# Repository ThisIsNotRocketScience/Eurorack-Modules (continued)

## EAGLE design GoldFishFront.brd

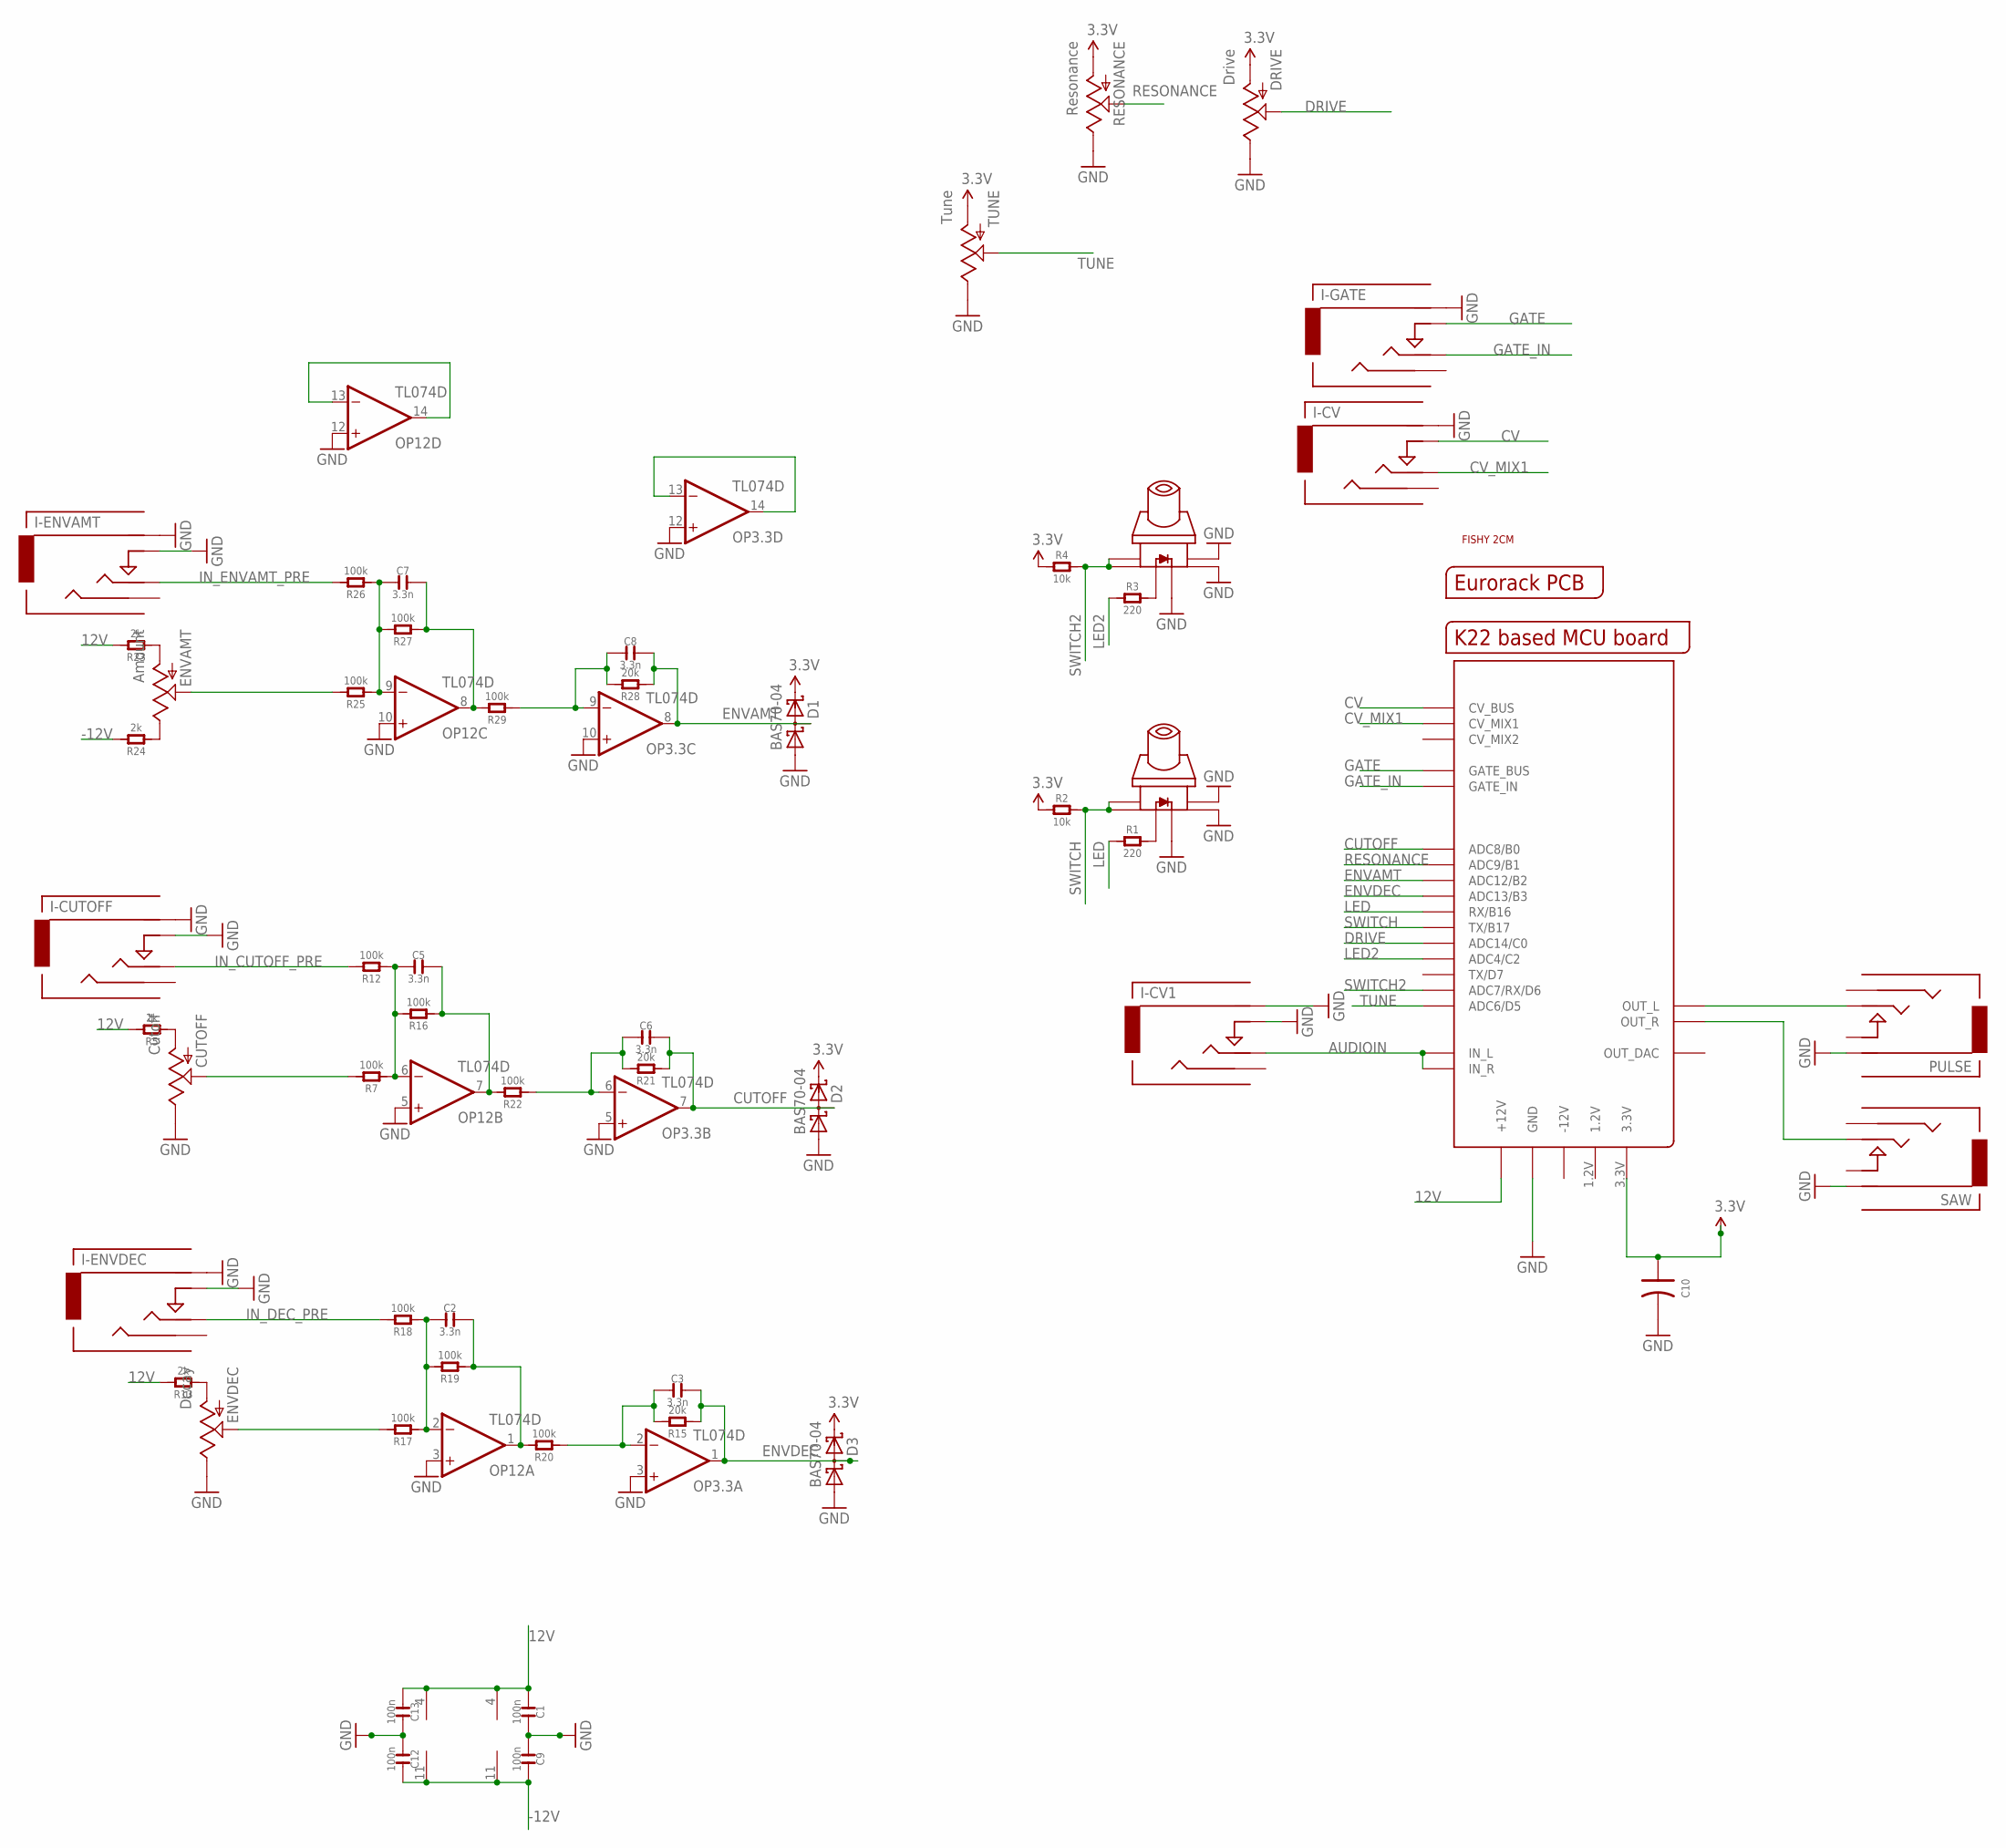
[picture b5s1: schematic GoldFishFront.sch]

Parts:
C1, C9, C12, C13: 100n; C0603
C2, C3, C5, C6, C7, C8: 3.3n; C0603
C10: C-POLAR-A; AVX-A
CUTOFF: Cutoff; OG-POTS_ALPS_POT_VERTICAL
D1, D2, D3: BAS70-04; SOT23
DRIVE: Drive; OG-POTS_ALPS_POT_VERTICAL
ENVAMT: Amount; OG-POTS_ALPS_POT_VERTICAL
ENVDEC: Decay; OG-POTS_ALPS_POT_VERTICAL
I-CUTOFF: Cutoff; 3.5MM-JACK-SWITCH-13MM-INPUT
I-CV: CV; 3.5MM-JACK-SWITCH-13MM-INPUT
I-CV1: External; 3.5MM-JACK-SWITCH-13MM-INPUT
I-ENVAMT: Amount; 3.5MM-JACK-SWITCH-13MM-INPUT
I-ENVDEC: Decay; 3.5MM-JACK-SWITCH-13MM-INPUT
I-GATE: Gate; 3.5MM-JACK-SWITCH-13MM-INPUT
OP3.3, OP12: TL074D; SO14
PULSE: Pulse; 3.5MM-JACK-SWITCH-13MM-OUTPUT
R1, R3: 220; R0603
R2, R4: 10k; R0603
R5, R13, R23, R24: 2k; R0603
R7, R12, R16, R17, R18, R19, R20, R22, R25, R26, R27, R29: 100k; R0603
R15, R21, R28: 20k; R0603
RESONANCE: Resonance; OG-POTS_ALPS_POT_VERTICAL
SAW: Saw; 3.5MM-JACK-SWITCH-13MM-OUTPUT
TUNE: Tune; OG-POTS_ALPS_POT_VERTICAL
U$1: MCUBOARD; MCUBASEBOARD
U$2: EURORACK_PCB12HP; EURORACK12HPPCB
U$3: FISH2CM_SILK; FISH_WITHSILK
U$6, U$17: SWITCH_W_LED_PB6149L-X-102WHITE; PB6149L

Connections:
3.3V: C10.+ (1), D1.2 (C2), D2.2 (C2), D3.2 (C2), DRIVE.P$3 (A), R2.1, R4.1, RESONANCE.P$3 (A), TUNE.P$3 (A), U$1.3.3V
12V: C1.1, C13.1, OP3.3.4 (V+), OP12.4 (V+), R5.2, R13.2, R23.2, U$1.+12V@1 (+12V), U$1.+12V@2 (+12V)
-12V: C9.2, C12.2, OP3.3.11 (V-), OP12.11 (V-), R24.2
AUDIOIN: I-CV1.TIP@1 (TIP), I-CV1.TIP@2 (TIP), U$1.IN_L, U$1.IN_R
CUTOFF: C6.2, D2.3 (C1A2), OP3.3.7 (OUT), R21.1, U$1.ADC8 (ADC8/B0)
CV: I-CV.SWITCH@1 (SWITCH), I-CV.SWITCH@2 (SWITCH), U$1.CVBUS (CV_BUS)
CV_MIX1: I-CV.TIP@1 (TIP), I-CV.TIP@2 (TIP), U$1.CV_MIX1
DRIVE: DRIVE.P$2 (S), U$1.ADC14 (ADC14/C0)
ENVAMT: C8.2, D1.3 (C1A2), OP3.3.8 (OUT), R28.1, U$1.ADC12 (ADC12/B2)
ENVDEC: C3.2, D3.3 (C1A2), OP3.3.1 (OUT), R15.1, U$1.ADC13 (ADC13/B3)
GATE: I-GATE.SWITCH@1 (SWITCH), I-GATE.SWITCH@2 (SWITCH), U$1.GATE_BUS
GATE_IN: I-GATE.TIP@1 (TIP), I-GATE.TIP@2 (TIP), U$1.GATE_IN
GND: C1.2, C9.1, C10.- (2), C12.1, C13.2, CUTOFF.P$1 (E), D1.1 (A1), D2.1 (A1), D3.1 (A1), DRIVE.P$1 (E), ENVDEC.P$1 (E), I-CUTOFF.RING@1 (RING), I-CUTOFF.RING@2 (RING), I-CUTOFF.SWITCH@1 (SWITCH), I-CUTOFF.SWITCH@2 (SWITCH), I-CV.RING@1 (RING), I-CV.RING@2 (RING), I-CV1.RING@1 (RING), I-CV1.RING@2 (RING), I-CV1.SWITCH@1 (SWITCH), I-CV1.SWITCH@2 (SWITCH), I-ENVAMT.RING@1 (RING), I-ENVAMT.RING@2 (RING), I-ENVAMT.SWITCH@1 (SWITCH), I-ENVAMT.SWITCH@2 (SWITCH), I-ENVDEC.RING@1 (RING), I-ENVDEC.RING@2 (RING), I-ENVDEC.SWITCH@1 (SWITCH), I-ENVDEC.SWITCH@2 (SWITCH), I-GATE.RING@1 (RING), I-GATE.RING@2 (RING), OP3.3.3 (+IN), OP3.3.5 (+IN), OP3.3.10 (+IN), OP3.3.12 (+IN), OP12.3 (+IN), OP12.5 (+IN), OP12.10 (+IN), OP12.12 (+IN), PULSE.RING@1 (RING), PULSE.RING@2 (RING), RESONANCE.P$1 (E), SAW.RING@1 (RING), SAW.RING@2 (RING), TUNE.P$1 (E), U$1.GND@1 (GND), U$1.GND@2 (GND), U$1.GND@4 (GND), U$1.GND@5 (GND), U$1.GND@6 (GND), U$1.GND@7 (GND), U$1.GND@8 (GND), U$1.GND@9 (GND), U$1.GND_BUS (GND), U$6.3, U$6.4, U$6.LEDNEG (NEG), U$17.3, U$17.4, U$17.LEDNEG (NEG)
IN_CUTOFF_PRE: I-CUTOFF.TIP@1 (TIP), I-CUTOFF.TIP@2 (TIP), R12.2
IN_DEC_PRE: I-ENVDEC.TIP@1 (TIP), I-ENVDEC.TIP@2 (TIP), R18.2
IN_ENVAMT_PRE: I-ENVAMT.TIP@1 (TIP), I-ENVAMT.TIP@2 (TIP), R26.2
LED: R1.1, U$1.RX/B16
LED2: R3.1, U$1.ADC4 (ADC4/C2)
unnamed: R3.2, U$6.LEDPOS (POS)
unnamed: CUTOFF.P$3 (A), R5.1
unnamed: OP12.13 (-IN), OP12.14 (OUT)
unnamed: OP3.3.13 (-IN), OP3.3.14 (OUT)
unnamed: ENVDEC.P$3 (A), R13.1
unnamed: R1.2, U$17.LEDPOS (POS)
unnamed: ENVDEC.P$2 (S), R17.2
unnamed: C2.1, OP12.2 (-IN), R17.1, R18.1, R19.2
unnamed: C2.2, OP12.1 (OUT), R19.1, R20.2
unnamed: C3.1, OP3.3.2 (-IN), R15.2, R20.1
unnamed: CUTOFF.P$2 (S), R7.2
unnamed: C5.1, OP12.6 (-IN), R7.1, R12.1, R16.2
unnamed: C5.2, OP12.7 (OUT), R16.1, R22.2
unnamed: C6.1, OP3.3.6 (-IN), R21.2, R22.1
unnamed: ENVAMT.P$3 (A), R23.1
unnamed: ENVAMT.P$1 (E), R24.1
unnamed: ENVAMT.P$2 (S), R25.2
unnamed: C7.1, OP12.9 (-IN), R25.1, R26.1, R27.2
unnamed: C7.2, OP12.8 (OUT), R27.1, R29.2
unnamed: C8.1, OP3.3.9 (-IN), R28.2, R29.1
RESONANCE: RESONANCE.P$2 (S), U$1.ADC9 (ADC9/B1)
SWITCH: R2.2, U$1.TX/B17, U$17.1, U$17.2
SWITCH2: R4.2, U$1.ADC7 (ADC7/RX/D6), U$6.1, U$6.2
TUNE: TUNE.P$2 (S), U$1.ADC6 (ADC6/D5)

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
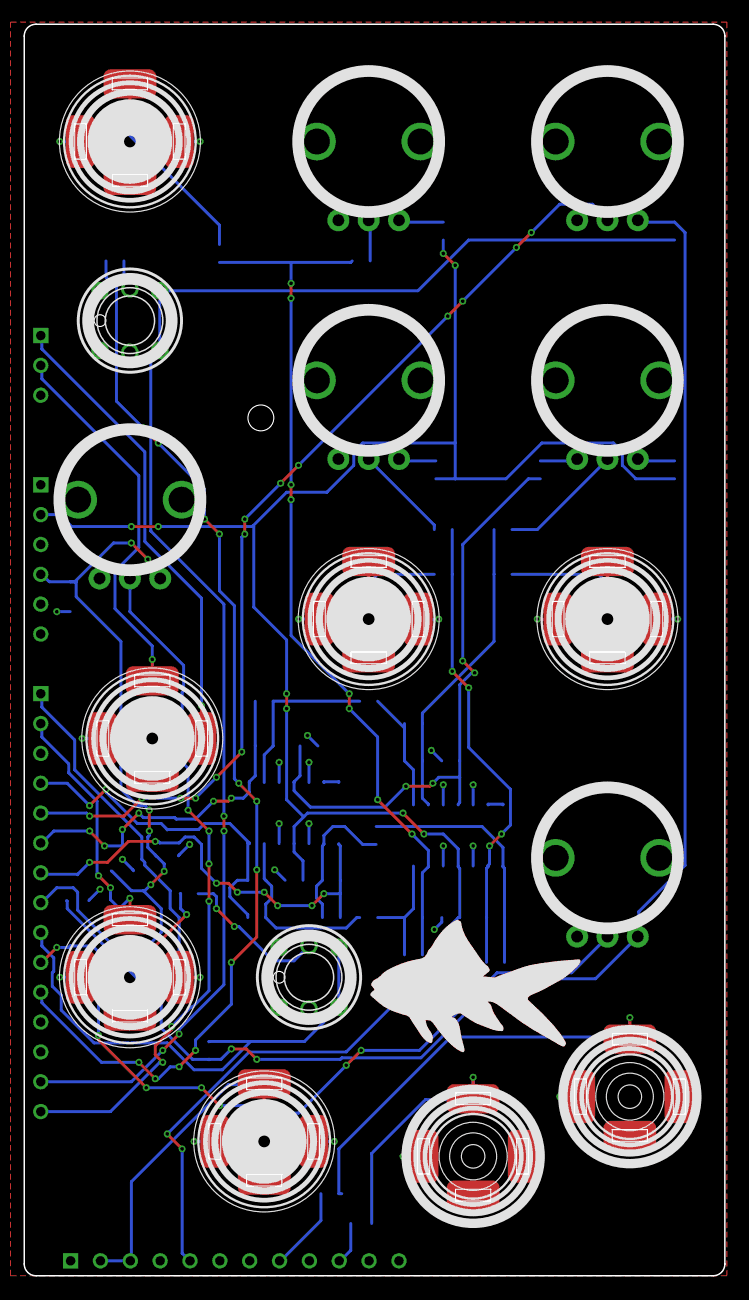
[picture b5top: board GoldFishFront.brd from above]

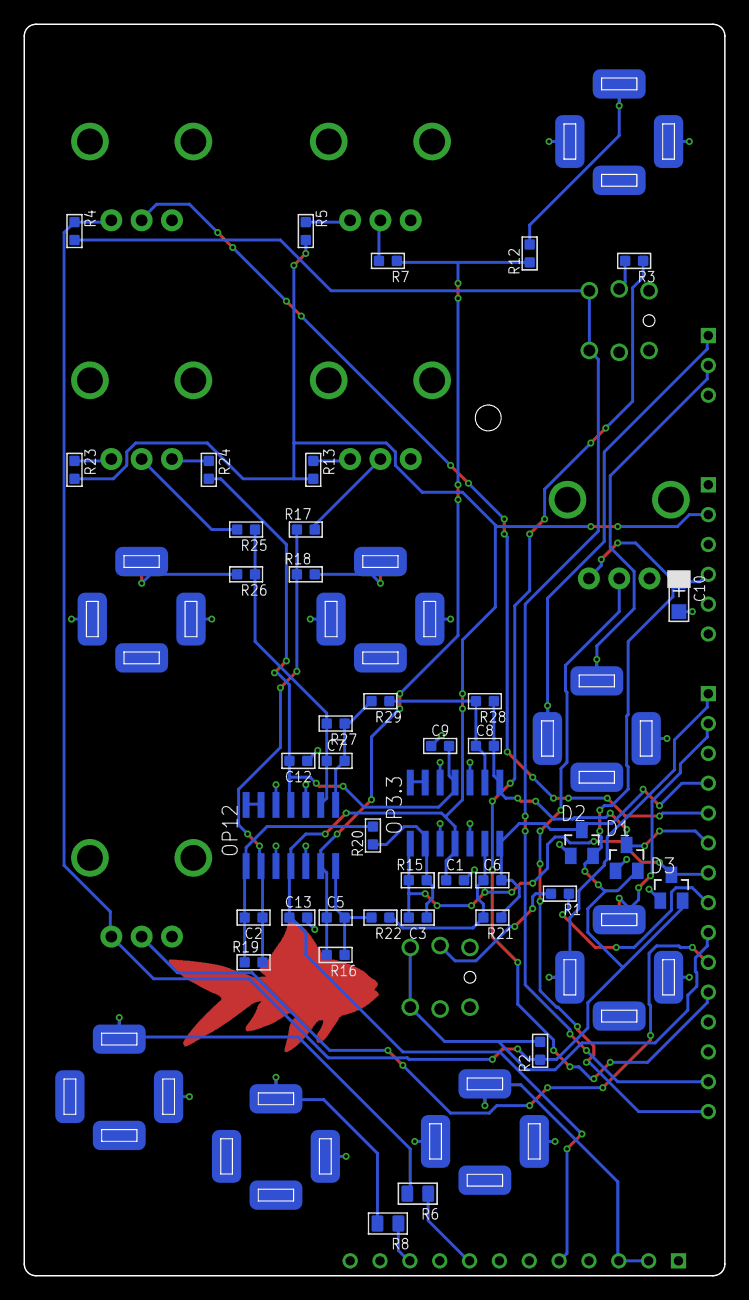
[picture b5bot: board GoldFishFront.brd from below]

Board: 2 copper layers, 59.6 x 106.5 mm, 60 parts (41 on the bottom side), 46 nets.

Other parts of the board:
R6, R8: 300; C0805
